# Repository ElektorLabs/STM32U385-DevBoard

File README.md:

# Elektor STM32U385 Dev Board: Arduino support

Arduino IDE support for the Elektor STM32U385 development board (schematic
260660-002, Rev 1.0), built on the official
[STM32duino](https://github.com/stm32duino/Arduino_Core_STM32) core.

What you get:

- **Board package (`elektor:stm32:u385board`):**
  - Every pin is named after the board, so you don't need the schematic:
    `LED1_A`, `BUTTON_USER1`, `SD_CS`, `GROVE_I2C_POWER`, `MIKROBUS_CS`, ...
  - `Serial` is the USB serial port; `Serial1`, `Wire` and `SPI` sit on the
    right header pins.
  - Uploads go over USB: BOOT + RESET, then *Upload*. An optional
    auto-reset method needs no buttons at all.
- **Elektor STM32U385 Dev Board library** (`U385Board.h`): LEDs, debounced
  buttons, clock switching, MCO output, temperature, VDDA, unique ID, reset
  cause and SMPS/LDO selection.
- **Nine examples:** LED cycle, LEDs with buttons, USB serial, board info,
  clock switching, low-power modes, Grove I2C scanner, microSD card and a
  mikroBUS Click tester.

| | |
|---|---|
| MCU | STM32U385RGT6Q: Cortex-M33, 96 MHz, 1 MB flash, 256 KB SRAM, SMPS package |
| USB | USB-C, full speed (CDC serial and ROM DFU bootloader) |
| Clocks | MSIS 96 MHz (default), HSI48 + CRS for USB, 16 MHz HSE crystal, 32.768 kHz LSE crystal |
| On board | 2 × two-colour LEDs (4 channels), User1/User2/Boot/Reset buttons, microSD, Grove I2C (switched), Grove/UART header, Qwiic, mikroBUS, Arduino Uno headers, LiPo charger |

## Documentation

| Document | Read it when |
|---|---|
| This README | Overview, pin names, library overview, examples, known issues |
| [Windows install](docs/windows-install.md) | Installing on Windows, in five steps |
| [Install guide](src/README.md) | Installing on Linux, macOS or Windows; arduino-cli, git links, Tools menu |
| [Pinout drawing](docs/pinout.png) ([SVG](docs/pinout.svg)) | Quick look at every header pin, connector, LED and button |
| [Pin guide](docs/pin-guide.md) | Wiring something up: every header pin, connector, on-board part and board name, plus the power section |
| [Board top](docs/board-top.png) / [bottom](docs/board-bottom.png) | Finding a part or connector on the PCB |
| [Schematic](docs/schematic-260660-002.png) | You need to trace a signal or check a component value |
| [How uploading works](docs/uploading.md) | Upload fails, the board stays in DFU, or you want to know what the button-free upload does |
| [Board and software overview](docs/board-and-software-overview.md) | Everything in one document: v1.1 changes, board package, library, all examples with code, upload internals, bring-up (source for the article) |
| [Problems and solutions](docs/problems-and-solutions.md) | Background: every hurdle during bring-up and how it was solved, including the drawbacks of button-free upload |
| [`U385Board.h`](src/Arduino/libraries/Elektor_STM32U385_DevBoard/src/U385Board.h) | Library reference: every function, with a comment explaining it |
| [`variant_U385_BOARD.h`](src/Arduino15/packages/elektor/hardware/stm32/1.0.0/variants/U385_BOARD/variant_U385_BOARD.h) | All pin numbers and board names as the compiler sees them |
| [Examples](src/Arduino/libraries/Elektor_STM32U385_DevBoard/examples) | Working code for every part of the board (also under *File → Examples → Elektor STM32U385 Dev Board*) |

## Repository layout

```
hardware/                          KiCad design files (board v1.1)
src/                               software; install guide in src/README.md
  Arduino15/                       paste "packages" into your Arduino15 folder
    packages/elektor/hardware/stm32/1.0.0/   the board package
      boards.txt, platform.txt     board definition, upload tool
      variants/U385_BOARD/         pin map, clock setup, button-free upload hook
      tools/dfu-upload.sh          upload script (dfu-util)
      tools/win/                   Windows: put dfu-util.exe here
      tools/linux/99-elektor-u385.rules   udev rule for Linux
  Arduino/                         paste "libraries" into your sketchbook
    libraries/Elektor_STM32U385_DevBoard/    the Arduino library
      src/U385Board.h, .cpp
      examples/                    00_LedCycle ... 08_MikroBus
docs/                              guides, pinout, schematic, board renders
  pin-guide.md                     every pin, connector and board name
  windows-install.md               Windows install in five steps
  uploading.md                     how the button-free upload works, recovery
  problems-and-solutions.md        hurdles during bring-up and how they were solved
  board-and-software-overview.md   everything in one document, with code
  schematic-260660-002.png         schematic
  pinout.png, pinout.svg           pinout drawing (made by docs/make_pinout.py)
  board-top.png, -bottom.png       board renders
```

## Getting started

1. Install **STM32 MCU based boards** 3.1.0 or newer from the Boards Manager.
2. Copy two folders from `src` (each merges with the folder already there):

   | Copy this | Windows | Linux | macOS |
   |---|---|---|---|
   | `src/Arduino15/packages` | `%LOCALAPPDATA%\Arduino15` | `~/.arduino15` | `~/Library/Arduino15` |
   | `src/Arduino/libraries` | `Documents\Arduino` | `~/Arduino` | `~/Documents/Arduino` |

3. Install dfu-util and the USB driver (Windows) or udev rule (Linux).
4. Put the board in DFU mode once (hold BOOT, press RESET) and upload
   *File → Examples → Elektor STM32U385 Dev Board → 00_LedCycle*.

Step by step: [Windows install](docs/windows-install.md) ·
[all systems, plus arduino-cli and git](src/README.md).

## Using the board

### Pin names

Use the board names; the STM32 names (`PA5`) and Arduino numbers (`13`) also
work. [docs/pin-guide.md](docs/pin-guide.md) has the full table with
connectors and schematic references.

The Arduino Uno headers are numbered as on any Uno, and each number is
mapped to the STM32 pin wired to that header position. These three lines
all drive the same pin, the D13 header pin (PA5):

```cpp
digitalWrite(13, HIGH);     // Arduino number
digitalWrite(D13, HIGH);    // Arduino name
digitalWrite(PA5, HIGH);    // STM32 name
```

| Header | STM32 | | Header | STM32 | | Header | STM32 |
|---|---|---|---|---|---|---|---|
| D0 | PA10 | | D6 | PB10 | | D12 | PA6 |
| D1 | PA9 | | D7 | PC6 | | D13 | PA5 |
| D2 | PC9 | | D8 | PC7 | | D14 | PB7 |
| D3 | PB13 | | D9 | PA8 | | D15 | PB6 |
| D4 | PB14 | | D10 | PA15 | | A0 / A1 / A2 | PA0 / PA1 / PA2 |
| D5 | PB15 | | D11 | PA7 | | A3 / A4 / A5 | PC1 / PA3 / PB1 |

The mapping is in
[`variant_U385_BOARD.h`](src/Arduino15/packages/elektor/hardware/stm32/1.0.0/variants/U385_BOARD/variant_U385_BOARD.h)
and was verified for every header pin with compile-time checks
(`static_assert(D13 == PA5)`, `static_assert(A3 == PC1)`, ...). The same pairs are printed on the pinout drawing.

| Name | Pin | What |
|---|---|---|
| `LED1_A` (`LED_BUILTIN`), `LED1_B` | PC10, PC11 | LED1, active high |
| `LED2_A`, `LED2_B` | PC12, PB4 | LED2, active high |
| `BUTTON_USER1` (`USER_BTN`) | PB5 | SW2 "User1", HIGH when pressed |
| `BUTTON_USER2` | PB2 | SW1 "User2", HIGH when pressed |
| `GROVE_I2C_POWER` | PA4 | HIGH turns on 3V3 at the Grove I2C socket K4 |
| `SD_CS`, `SD_DETECT` | PC8, PD2 | microSD over SPI; detect LOW = card in |
| `MIKROBUS_AN/RST/CS/PWM/INT` | PA0, PC3, PB0, PB10, PC9 | mikroBUS sockets J5/J6 |
| `MCO_PIN` | PA8 (D9) | clock output |
| `D0`–`D15`, `A0`–`A5` | Arduino Uno headers | |

| Object | Pins | Connected to |
|---|---|---|
| `Serial` | USB | USB-C (virtual COM port) |
| `Serial1` | PA10 RX / PA9 TX | D0/D1, UART header K6, mikroBUS J6 |
| `Wire` | PB7 SDA / PB6 SCL | Grove I2C K4, Qwiic K8, mikroBUS, J4; 4.7 kΩ pull-ups on board |
| `SPI` | PA5 SCK / PA6 MISO / PA7 MOSI, SS PA15 | D10–D13, mikroBUS J5, microSD |

Plain Arduino, no library needed:

```cpp
void setup() {
  pinMode(LED1_A, OUTPUT);
  pinMode(BUTTON_USER1, INPUT);           // external 10k pull-down on board
}
void loop() {
  digitalWrite(LED1_A, digitalRead(BUTTON_USER1) == BUTTON_PRESSED);
}
```

### The library (`U385Board.h`)

```cpp
#include <U385Board.h>

void setup() {
  Serial.begin(115200);
  Board.begin();                    // LEDs off, buttons as inputs
}

void loop() {
  Board.update();                   // debounce the buttons, call every loop
  if (Board.pressed(USER1)) Board.ledToggle(0);
  if (Board.heldFor(USER2) > 1000) Board.ledsAll(true);
}
```

| Area | Functions |
|---|---|
| LEDs (index 0–3 = PC10, PC11, PB4, PC12) | `led(i, on)`, `ledToggle(i)`, `ledState(i)`, `ledsOff()`, `ledsAll(on)`, `ledsShow(bits)`, `ledPin(i)` |
| Buttons (`USER1`, `USER2`) | `update()`, `isDown(b)`, `pressed(b)`, `released(b)`, `heldFor(b)`, `readRaw(b)`, `releasedLevel(b)`, `setDebounce(ms)` |
| Board | `groveI2CPower(on)`, `sdCardPresent()`, `enterBootloader()`, `useSMPS(on)`, `smpsActive()` |
| Clocks | `setSystemClock(SYSCLK_96MHZ … SYSCLK_3MHZ)`, `systemClock()`, `hclk()`, `pclk1/2/3()`, `systemClockSource()`, `startLSE()`, `startHSE()`, `msiPllLock()`, `clockOut(source, div)`, `printClocks(Serial)` |
| Chip | `uniqueId()`, `flashSizeKB()`, `resetCause()`, `temperatureC()`, `vdda()` |

Notes:

- **Button polarity.** `Board.begin()` takes the button level at start-up as
  "released", so the library works whichever way the buttons are wired.
  Don't hold a button while the sketch starts.
- **Slow clocks and USB.** USB needs at least 12 MHz. At 6 MHz and 3 MHz the
  USB serial port stops until you go back up.
- **After `setSystemClock()`,** call `Serial1.begin()` / `Wire.setClock()`
  again so their dividers match the new clock. `millis()` and `delay()`
  adjust by themselves.
- **SMPS.** `useSMPS()` switches the core supply from the LDO to the on-board
  SMPS (L1). Expect lower current, mainly at 96 MHz. Switching was tested both
  ways at 96 MHz; the current saving has not been measured yet.
- **After Shutdown** the sketch restarts and `resetCause()` reports
  "power-on / brown-out", the way the chip flags a shutdown exit.

### Examples

*File → Examples → Elektor STM32U385 Dev Board*:

| Example | What it shows | Tested on hardware |
|---|---|---|
| `00_LedCycle` | The four LEDs run through seven patterns: chase, bounce, fill, alternate, LED1 vs LED2, binary count, flash | ✅ |
| `01_LedCycleButtons` | User1 = next LED, User2 = previous, hold User1 1 s = auto-run; button levels printed on serial | ⏳ not yet tested with the buttons |
| `02_SerialMonitor` | USB serial command shell: `1`–`4` toggle LEDs, `a` all, `o` off, `c` clocks, `i` info, `b` bootloader | ✅ |
| `03_BoardInfo` | Clocks, unique ID, flash size, reset cause, die temperature, VDDA, regulator, SD card | ✅ |
| `04_ClockSwitch` | Steps SYSCLK 96 → 48 → 24 → 12 MHz with `n`; `l` locks MSI to the LSE crystal; MCO on D9 | ✅ |
| `05_LowPowerModes` | Sleep, Stop (deep sleep) and Shutdown, woken by a button or an RTC alarm after 10 s (all three modes over serial) | ✅ RTC wake; button wake not yet tested |
| `06_GroveI2CScanner` | Turns on Grove power and scans the I2C bus | ✅ |
| `07_SDCard` | microSD over SPI with SdFat (FAT16, FAT32 and exFAT): card info, file list, append/read/delete a log file, hot-plug via card detect | ✅ 64 GB SDXC, exFAT |
| `08_MikroBus` | Click board test tool: reset, AN and INT levels, I2C scan, SPI read-ID, PWM, and a USB-to-UART bridge for AT-command clicks | ✅ socket empty; no Click board tested yet |

## Known issues

- **A sketch that disables USB, crashes or sleeps** cannot be reset into DFU
  from the IDE. Use BOOT + RESET.
- **Stack size.** STM32duino 3.1.0's linker script for the U3 sets a 1 KB
  stack, and the startup code makes that a hard limit (MSPLIM). Going past it
  locks the chip up, USB included. It happened with SdFat creating a file.
  This board package raises the stack to 16 KB in its own linker script.
  Other STM32U3 boards in STM32duino still have the 1 KB limit.
- **Tested on Linux** with arduino-cli 1.3.0 and STM32duino 3.1.0, and on
  **Windows** with Arduino IDE 2.x: copy-and-paste install, upload in DFU
  mode and button-free upload. macOS is untested; please report how it goes.

## License

- The board package, library, examples and docs are released under the MIT
  License (see `LICENSE`).
- `src/Arduino15/packages/elektor/hardware/stm32/1.0.0/variants/U385_BOARD/PeripheralPins.c`, `PinNamesVar.h` and `ldscript.ld`
  come from the STM32duino core. They remain © STMicroelectronics under the
  BSD-3-Clause license given in each file's header.

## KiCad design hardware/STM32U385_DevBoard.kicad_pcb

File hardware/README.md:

# Hardware

KiCad project for the Elektor STM32U385 Dev Board (260660), board revision
v1.1.

| Path | What |
|---|---|
| `STM32U385_DevBoard.kicad_pro` | KiCad project: open this |
| `STM32U385_DevBoard.kicad_sch` | Schematic |
| `STM32U385_DevBoard.kicad_pcb` | PCB layout |
| `stm32u385-uno-schematic.pdf` | Schematic as PDF |
| `MySym/`, `MyLib.pretty/`, `DevBoard4.pretty/` | Project symbols and footprints |
| `3D Models/` | STEP models for the 3D view |
| `Data_Sheets/` | Datasheets of the main parts |
| `plots/` | Assembly drawing (PDF) |
| `production/` | Fabrication ZIP: Gerbers, drill and placement files |

v1.1 moves the buttons: RESET and BOOT sit on the left edge next to USB-C,
USER1 and USER2 at the bottom left next to the barrel jack, so they are
easier to press. The MCU pins are unchanged, so the same board package and
library work on v1.0 and v1.1. [docs/pin-guide.md](../docs/pin-guide.md) and
the [pinout drawing](../docs/pinout.png) list every pin and connector.

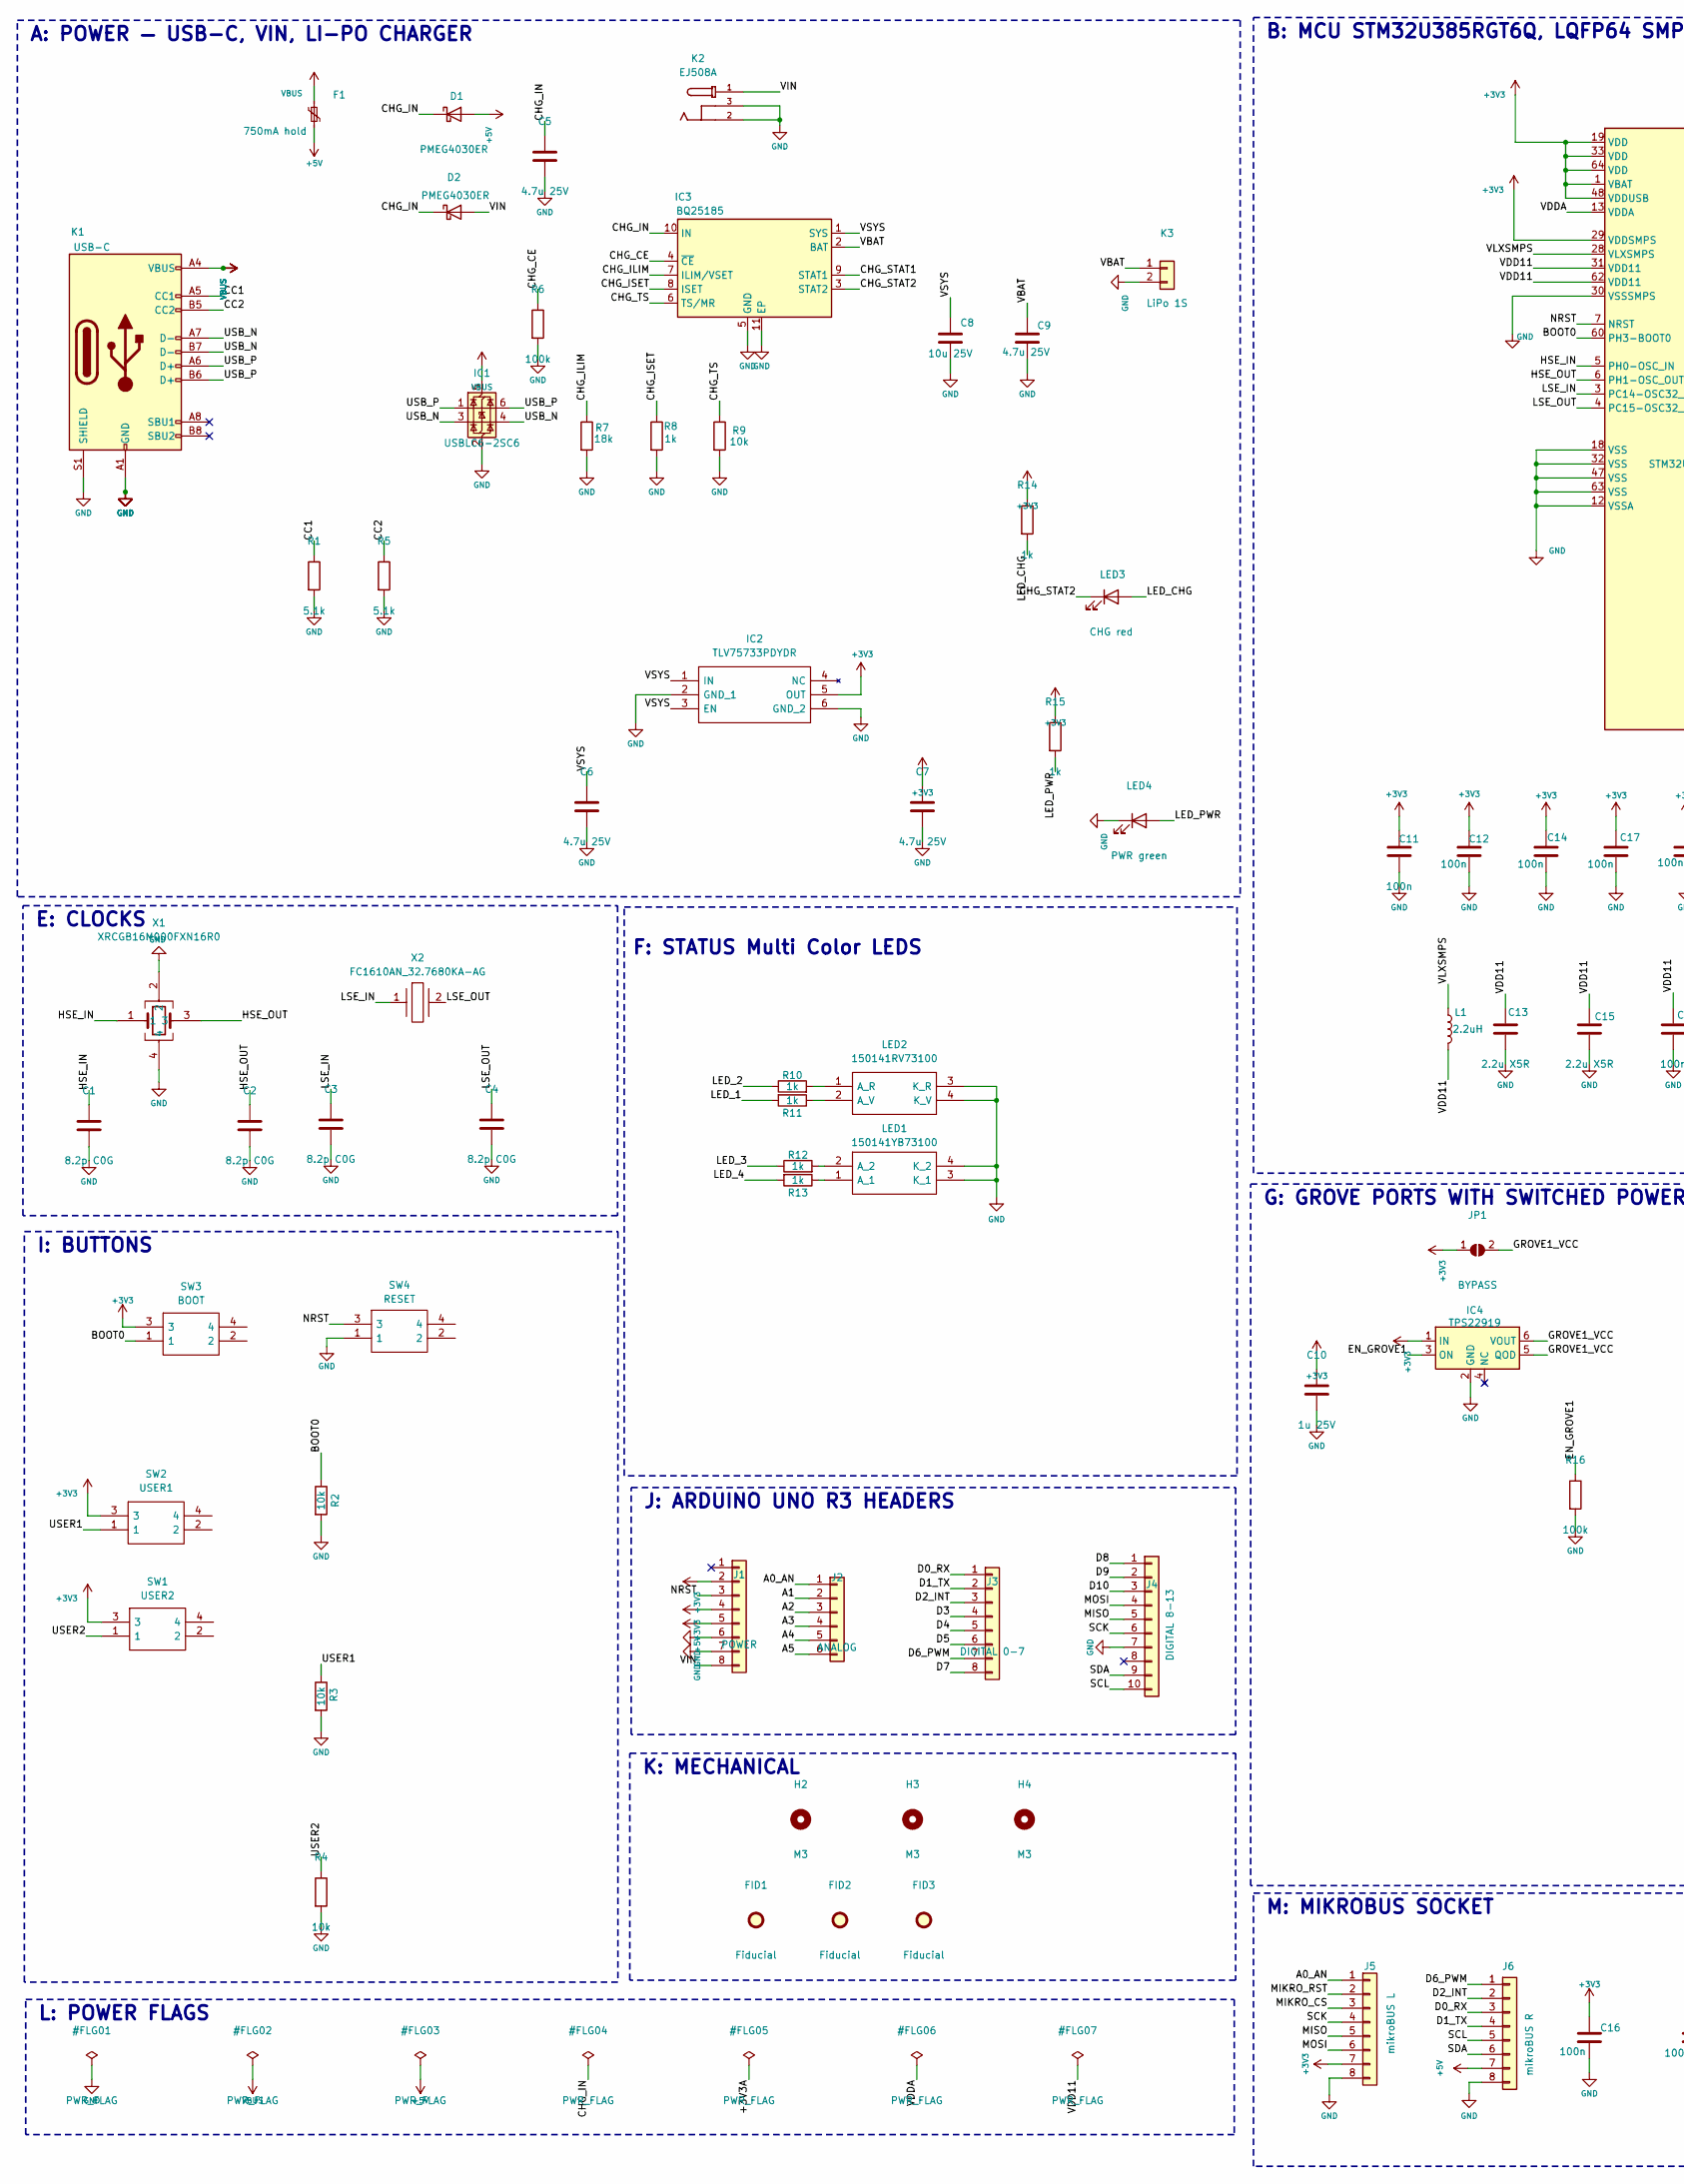
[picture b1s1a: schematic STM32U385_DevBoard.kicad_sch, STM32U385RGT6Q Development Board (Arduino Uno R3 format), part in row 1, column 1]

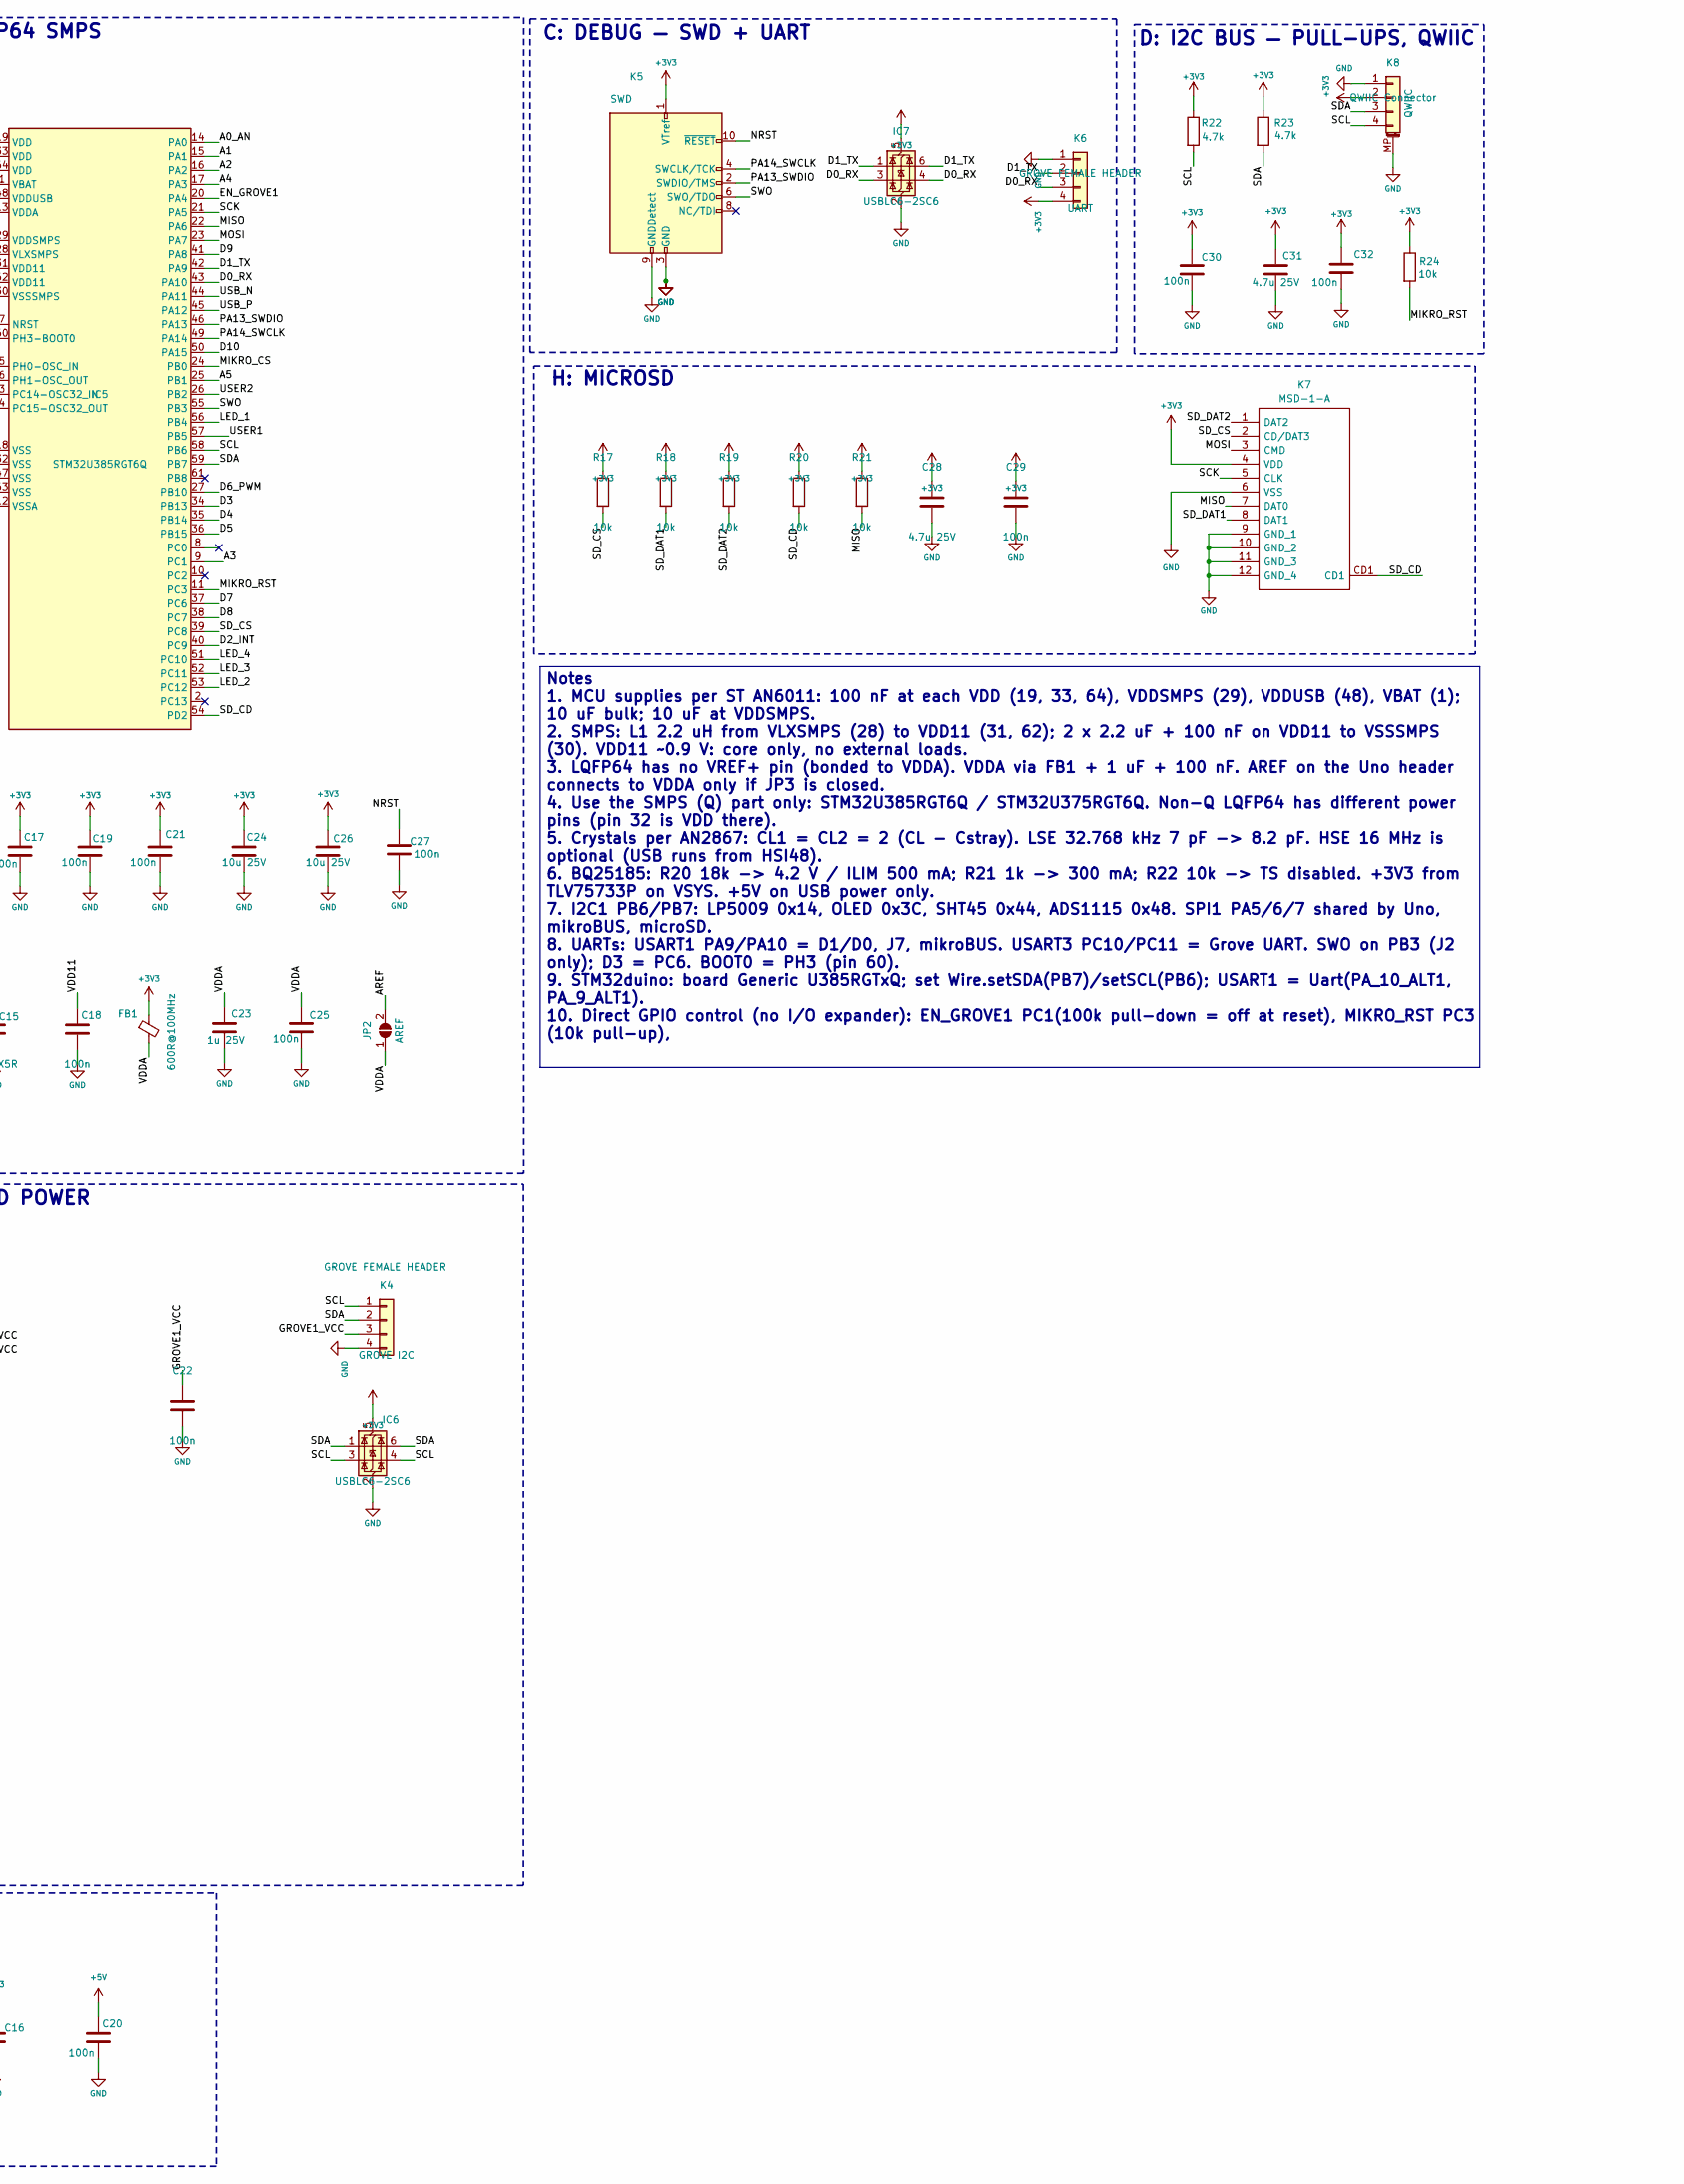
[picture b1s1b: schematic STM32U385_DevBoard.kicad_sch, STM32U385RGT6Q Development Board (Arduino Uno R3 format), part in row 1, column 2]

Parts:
C1, C2, C3, C4: 8.2p C0G; Capacitor_SMD__C_0402_1005Metric_c6f3790037; MPN GRM1555C1H8R2BA01D
C5, C6, C7, C9, C28, C31: 4.7u 25V; Capacitor_SMD__C_0603_1608Metric_922116857e; MPN GRM188R61E475KE11J
C8, C24, C26: 10u 25V; Capacitor_SMD__C_0805_2012Metric_aa5599db5b; MPN GRM21BR61E106KA73L
C10, C23: 1u 25V; Capacitor_SMD__C_0402_1005Metric_c6f3790037; MPN CL05A105KA5NQNC
C11, C12, C14, C16, C17, C18, C19, C20, C21, C22, C25, C27, C29, C30, C32: 100n; Capacitor_SMD__C_0402_1005Metric_c6f3790037; MPN GRM155R71C104KA88D
C13, C15: 2.2u X5R; Capacitor_SMD__C_0603_1608Metric_922116857e; MPN GRM188R61C225KE15D
D1, D2: PMEG4030ER; Diode_SMD__Nexperia_CFP3_SOD-123W_821266d4fc; MPN PMEG4030ER,115
F1: 750mA hold; Fuse__Fuse_0805_2012Metric_43cd33858f; MPN MF-PSMF075X-2
FB1: 600R@100MHz; Inductor_SMD__L_0603_1608Metric_cc9b436813; MPN BLM18KG601SN1D
FID1, FID2, FID3: Fiducial; Fiducial__Fiducial_1mm_Mask2mm_55869b6f71
H2, H3, H4: M3; DevBoard4__MountingHole_3.2mm_Uno_991e85bc9b
IC1, IC6, IC7: USBLC6-2SC6; Package_TO_SOT_SMD__SOT-23-6_bee7fafe0c; MPN USBLC6-2SC6
IC2: TLV75733PDYDR; Mouser Part Number 595-TLV75733PDYDR
IC3: BQ25185; DevBoard4__TI_DLH0010A_WSON-10_2x2.2mm_P0.4mm_301ec00fd8; MPN BQ25185DLHR
IC4: TPS22919; Package_TO_SOT_SMD__SOT-363_SC-70-6_8457b2c561; MPN TPS22919DCKR
IC5: STM32U385RGT6Q; Package_QFP__LQFP-64_10x10mm_P0.5mm_5fbfdbce52; MPN STM32U385RGT6Q
J1: POWER; Connector_PinSocket_2.54mm__PinSocket_1x08_P2.54mm_Vertical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; MPN 61300811821
J2: ANALOG; Connector_PinSocket_2.54mm__PinSocket_1x06_P2.54mm_Vertical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; MPN 61300611821
J3: DIGITAL 0-7; Connector_PinSocket_2.54mm__PinSocket_1x08_P2.54mm_Vertical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; MPN 61300811821
J4: DIGITAL 8-13; Connector_PinSocket_2.54mm__PinSocket_1x10_P2.54mm_Vertical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; MPN 61301011821
J5: mikroBUS L; Connector_PinSocket_2.54mm__PinSocket_1x08_P2.54mm_Vertical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; MPN 61300811821
J6: mikroBUS R; Connector_PinSocket_2.54mm__PinSocket_1x08_P2.54mm_Vertical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; MPN 61300811821
JP1: BYPASS; Jumper__SolderJumper-2_P1.3mm_Open_RoundedPad1.0x1.5mm_8996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
JP2: AREF; Jumper__SolderJumper-2_P1.3mm_Open_RoundedPad1.0x1.5mm_8996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
K1: USB-C; Connector_USB__USB_C_Receptacle_GCT_USB4105-xx-A_16P_TopMnt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; MPN USB4105-GF-A
K2: EJ508A; footprints10__MPD_EJ508A_cdcfbdb686; PARTREV J
K3: LiPo 1S; Connector_JST__JST_PH_S2B-PH-SM4-TB_1x02-1MP_P2.00mm_Horizo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; MPN S2B-PH-SM4-TB(LF)(SN)
K4: GROVE I2C; Connector_JST__JST_PH_S4B-PH-SM4-TB_1x04-1MP_P2.00mm_Horizo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; MPN 1597-114020164-ND
K5: SWD; Connector_PinHeader_1.27mm__PinHeader_2x05_P1.27mm_Vertical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; MPN 20021121-00010C4LF
K6: UART; Connector_JST__JST_PH_S4B-PH-SM4-TB_1x04-1MP_P2.00mm_Horizo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; MPN 1597-114020164-ND
K7: MSD-1-A; SamacSys_Parts__MSD1A_9faa34f890; Mouser Part Number 179-MSD-1-A
K8: QWIIC; Connector_JST__JST_SH_SM04B-SRSS-TB_1x04-1MP_P1.00mm_Horizo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; MPN SM04B-SRSS-TB
L1: 2.2uH; Inductor_SMD__L_0805_2012Metric_28a6f4f15e
LED1: 150141YB73100; SamacSys_Parts__150141RV73100_c801ef0791; Mouser Part Number 710-150141YB73100
LED2: 150141RV73100; SamacSys_Parts__150141RV73100_c801ef0791; Mouser Part Number 710-150141RV73100
LED3: CHG red; LED_SMD__LED_0603_1608Metric_041a55222f; MPN LTST-C191KRKT
LED4: PWR green; LED_SMD__LED_0603_1608Metric_041a55222f; MPN LTST-C191KGKT
R1, R5: 5.1k; Resistor_SMD__R_0402_1005Metric_a72d4a34ce; MPN RC0402FR-075K1L
R2, R3, R4, R9, R17, R18, R19, R20, R21, R24: 10k; Resistor_SMD__R_0402_1005Metric_a72d4a34ce; MPN RC0402FR-0710KL
R6, R16: 100k; Resistor_SMD__R_0402_1005Metric_a72d4a34ce; MPN RC0402FR-07100KL
R7: 18k; Resistor_SMD__R_0402_1005Metric_a72d4a34ce; MPN RC0402FR-0718KL
R8, R14, R15: 1k; Resistor_SMD__R_0402_1005Metric_a72d4a34ce; MPN RC0402FR-071KL
R10, R11, R12, R13: 1k; Resistor_SMD__R_0402_1005Metric_a72d4a34ce; MPN RC0402FR-0710KL
R22, R23: 4.7k; Resistor_SMD__R_0402_1005Metric_a72d4a34ce; MPN RC0402FR-074K7L
SW1: USER2; SKTHBAE010; Mouser Part Number 688-SKTHBAE010
SW2: USER1; SKTHBAE010; Mouser Part Number 688-SKTHBAE010
SW3: BOOT; SKTHBAE010; Mouser Part Number 688-SKTHBAE010
SW4: RESET; SKTHBAE010; Mouser Part Number 688-SKTHBAE010
X1: XRCGB16M000FXN16R0; XRCGB; Mouser Part Number 81-XRCGB16M000FXN16R
X2: FC1610AN_32.7680KA-AG; FC1610AN327680KAAG; Mouser Part Number 732-AN32.7680KA-AG

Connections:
+3V3: C7.1, C10.1, C11.1, C12.1, C14.1, C16.1, C17.1, C19.1, C21.1, C24.1, C26.1, C28.1, C29.1, C30.1, C31.1, C32.1, FB1.1, IC2.5 (OUT), IC4.1 (IN), IC5.1 (VBAT), IC5.19 (VDD), IC5.29 (VDDSMPS), IC5.33 (VDD), IC5.48 (VDDUSB), IC5.64 (VDD), IC6.5 (VBUS), IC7.5 (VBUS), J1.2, J1.4, J5.7, JP1.1 (A), K5.1 (VTref), K6.4, K7.4 (VDD), K8.2, R14.1, R15.1, R17.1, R18.1, R19.1, R20.1, R21.1, R22.1, R23.1, R24.1, SW1.3, SW2.3, SW3.3
+5V: C20.1, D1.2 (A), F1.2, J1.5, J6.7
/A0_AN: IC5.14 (PA0), J2.1, J5.1
/A1: IC5.15 (PA1), J2.2
/A2: IC5.16 (PA2), J2.3
/A3: IC5.9 (PC1), J2.4
/A4: IC5.17 (PA3), J2.5
/A5: IC5.25 (PB1), J2.6
/AREF: JP2.2 (B)
/BOOT0: IC5.60 (PH3-BOOT0), R2.1, SW3.1
/CC1: K1.A5 (CC1), R1.1
/CC2: K1.B5 (CC2), R5.1
/CHG_CE: IC3.4 (~CE), R6.1
/CHG_ILIM: IC3.7 (ILIM/VSET), R7.1
/CHG_IN: C5.1, D1.1 (K), D2.1 (K), IC3.10 (IN)
/CHG_ISET: IC3.8 (ISET), R8.1
/CHG_STAT1: IC3.9 (STAT1)
/CHG_STAT2: IC3.3 (STAT2), LED3.1 (K)
/CHG_TS: IC3.6 (TS/MR), R9.1
/D0_RX: IC5.43 (PA10), IC7.3 (I/O2), IC7.4 (I/O2), J3.1, J6.3, K6.3
/D1_TX: IC5.42 (PA9), IC7.1 (I/O1), IC7.6 (I/O1), J3.2, J6.4, K6.2
/D2_INT: IC5.40 (PC9), J3.3, J6.2
/D3: IC5.34 (PB13), J3.4
/D4: IC5.35 (PB14), J3.5
/D5: IC5.36 (PB15), J3.6
/D6_PWM: IC5.27 (PB10), J3.7, J6.1
/D7: IC5.37 (PC6), J3.8
/D8: IC5.38 (PC7), J4.1
/D9: IC5.41 (PA8), J4.2
/D10: IC5.50 (PA15), J4.3
/EN_GROVE1: IC4.3 (ON), IC5.20 (PA4), R16.1
/GROVE1_VCC: C22.1, IC4.5 (QOD), IC4.6 (VOUT), JP1.2 (B), K4.3
/HSE_IN: C1.1, IC5.5 (PH0-OSC_IN), X1.1
/HSE_OUT: C2.1, IC5.6 (PH1-OSC_OUT), X1.3
/LED_1: IC5.56 (PB4), R11.2
/LED_2: IC5.53 (PC12), R10.1
/LED_3: IC5.52 (PC11), R12.1
/LED_4: IC5.51 (PC10), R13.2
/LED_CHG: LED3.2 (A), R14.2
/LED_PWR: LED4.2 (A), R15.2
/LSE_IN: C3.1, IC5.3 (PC14-OSC32_IN), X2.1
/LSE_OUT: C4.1, IC5.4 (PC15-OSC32_OUT), X2.2
/MIKRO_CS: IC5.24 (PB0), J5.3
/MIKRO_RST: IC5.11 (PC3), J5.2, R24.2
/MISO: IC5.22 (PA6), J4.5, J5.5, K7.7 (DAT0), R21.2
/MOSI: IC5.23 (PA7), J4.4, J5.6, K7.3 (CMD)
/NRST: C27.1, IC5.7 (NRST), J1.3, K5.10 (~RESET), SW4.3
/PA13_SWDIO: IC5.46 (PA13), K5.2 (SWDIO/TMS)
/PA14_SWCLK: IC5.49 (PA14), K5.4 (SWCLK/TCK)
/SCK: IC5.21 (PA5), J4.6, J5.4, K7.5 (CLK)
/SCL: IC5.58 (PB6), IC6.3 (I/O2), IC6.4 (I/O2), J4.10, J6.5, K4.1, K8.4, R22.2
/SDA: IC5.59 (PB7), IC6.1 (I/O1), IC6.6 (I/O1), J4.9, J6.6, K4.2, K8.3, R23.2
/SD_CD: IC5.54 (PD2), K7.CD1, R20.2
/SD_CS: IC5.39 (PC8), K7.2 (CD/DAT3), R17.2
/SD_DAT1: K7.8 (DAT1), R18.2
/SD_DAT2: K7.1 (DAT2), R19.2
/SWO: IC5.55 (PB3), K5.6 (SWO/TDO)
/USB_N: IC1.3 (I/O2), IC1.4 (I/O2), IC5.44 (PA11), K1.A7 (D-), K1.B7 (D-)
/USB_P: IC1.1 (I/O1), IC1.6 (I/O1), IC5.45 (PA12), K1.A6 (D+), K1.B6 (D+)
/USER1: IC5.57 (PB5), R3.1, SW2.1
/USER2: IC5.26 (PB2), R4.1, SW1.1
/VBAT: C9.1, IC3.2 (BAT), K3.1
/VDD11: C13.1, C15.1, C18.1, IC5.31 (VDD11), IC5.62 (VDD11), L1.2
/VDDA: C23.1, C25.1, FB1.2, IC5.13 (VDDA), JP2.1 (A)
/VIN: D2.2 (A), J1.8, K2.1
/VLXSMPS: IC5.28 (VLXSMPS), L1.1
/VSYS: C6.1, C8.1, IC2.1 (IN), IC2.3 (EN), IC3.1 (SYS)
GND: C1.2, C2.2, C3.2, C4.2, C5.2, C6.2, C7.2, C8.2, C9.2, C10.2, C11.2, C12.2, C13.2, C14.2, C15.2, C16.2, C17.2, C18.2, C19.2, C20.2, C21.2, C22.2, C23.2, C24.2, C25.2, C26.2, C27.2, C28.2, C29.2, C30.2, C31.2, C32.2, IC1.2 (GND), IC2.2 (GND_1), IC2.6 (GND_2), IC3.5 (GND), IC3.11 (EP), IC4.2 (GND), IC5.12 (VSSA), IC5.18 (VSS), IC5.30 (VSSSMPS), IC5.32 (VSS), IC5.47 (VSS), IC5.63 (VSS), IC6.2 (GND), IC7.2 (GND), J1.6, J1.7, J4.7, J5.8, J6.8, K1.A1 (GND), K1.A12 (GND), K1.B1 (GND), K1.B12 (GND), K1.S1 (SHIELD), K2.2, K2.3, K3.2, K4.4, K5.3 (GND), K5.5 (GND), K5.9 (GNDDetect), K6.1, K7.6 (VSS), K7.9 (GND_1), K7.10 (GND_2), K7.11 (GND_3), K7.12 (GND_4), K8.1, K8.MP (MountPin), LED1.3 (K_1), LED1.4 (K_2), LED2.3 (K_R), LED2.4 (K_V), LED4.1 (K), R1.2, R2.2, R3.2, R4.2, R5.2, R6.2, R7.2, R8.2, R9.2, R16.2, SW4.1, X1.2, X1.4
unnamed: LED1.1 (A_1), R13.1
unnamed: LED1.2 (A_2), R12.2
unnamed: LED2.1 (A_R), R10.2
unnamed: LED2.2 (A_V), R11.1
VBUS: F1.1, IC1.5 (VBUS), K1.A4 (VBUS), K1.A9 (VBUS), K1.B4 (VBUS), K1.B9 (VBUS)

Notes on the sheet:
G: GROVE PORTS WITH SWITCHED POWER
E: CLOCKS
H: MICROSD
I: BUTTONS
D: I2C BUS — PULL-UPS, QWIIC
L: POWER FLAGS
J: ARDUINO UNO R3 HEADERS
K: MECHANICAL
A: POWER — USB-C, VIN, LI-PO CHARGER
C: DEBUG — SWD + UART
B: MCU STM32U385RGT6Q, LQFP64 SMPS
M: MIKROBUS SOCKET
F: STATUS Multi Color LEDS
Notes 1. MCU supplies per ST AN6011: 100 nF at each VDD (19, 33, 64), VDDSMPS (29), VDDUSB (48), VBAT (1); 10 uF bulk; 10 uF at VDDSMPS. 2. SMPS: L1 2.2 uH from VLXSMPS (28) to VDD11 (31, 62); 2 x 2.2 uF + 100 nF on VDD11 to VSSSMPS (30). VDD11 ~0.9 V: core only, no external loads. 3. LQFP64 has no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

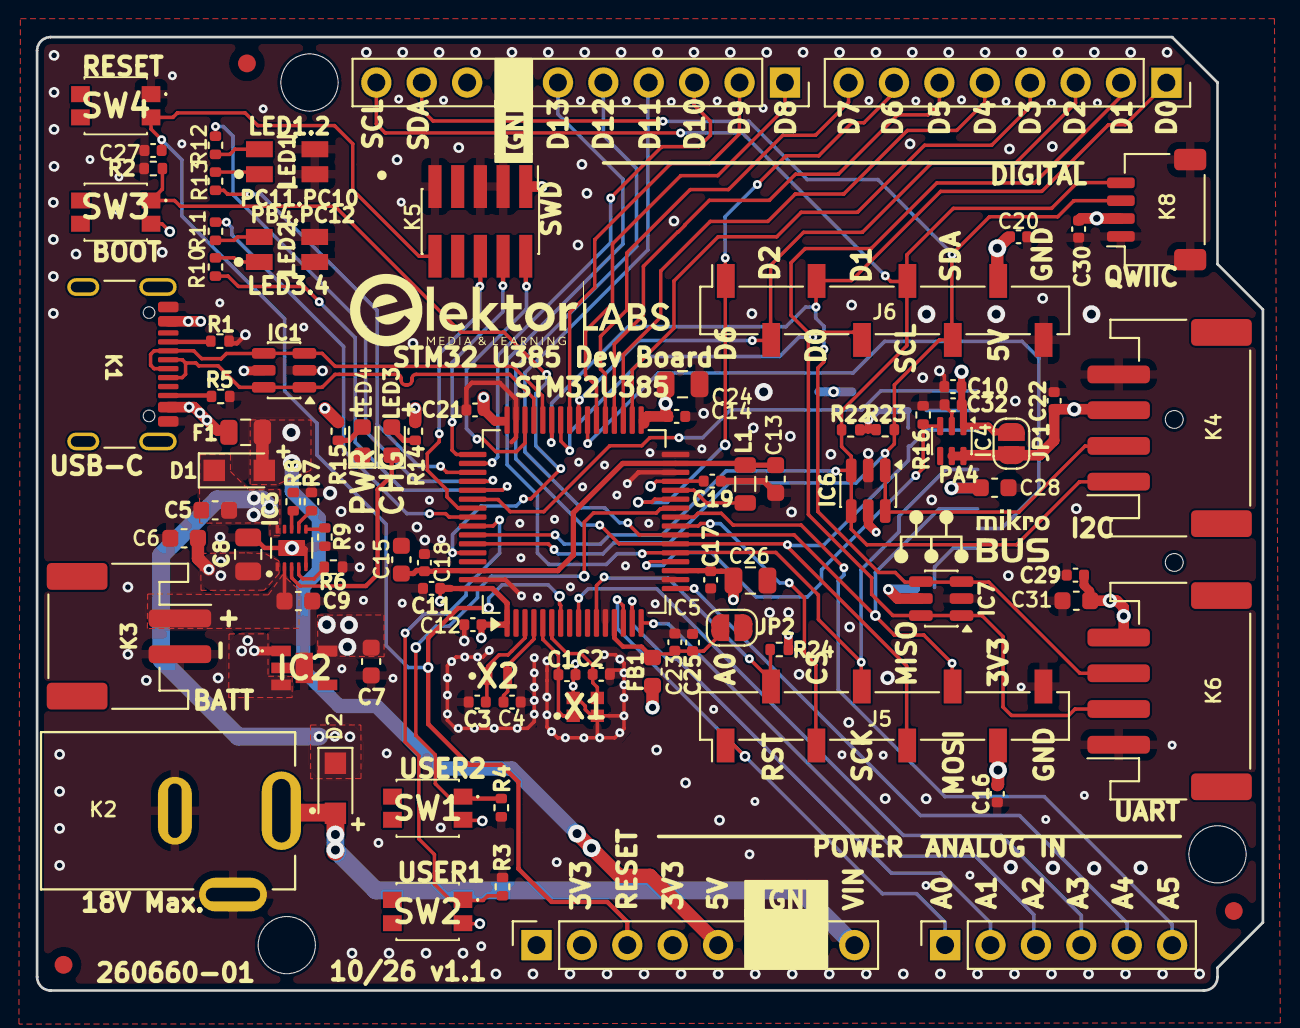
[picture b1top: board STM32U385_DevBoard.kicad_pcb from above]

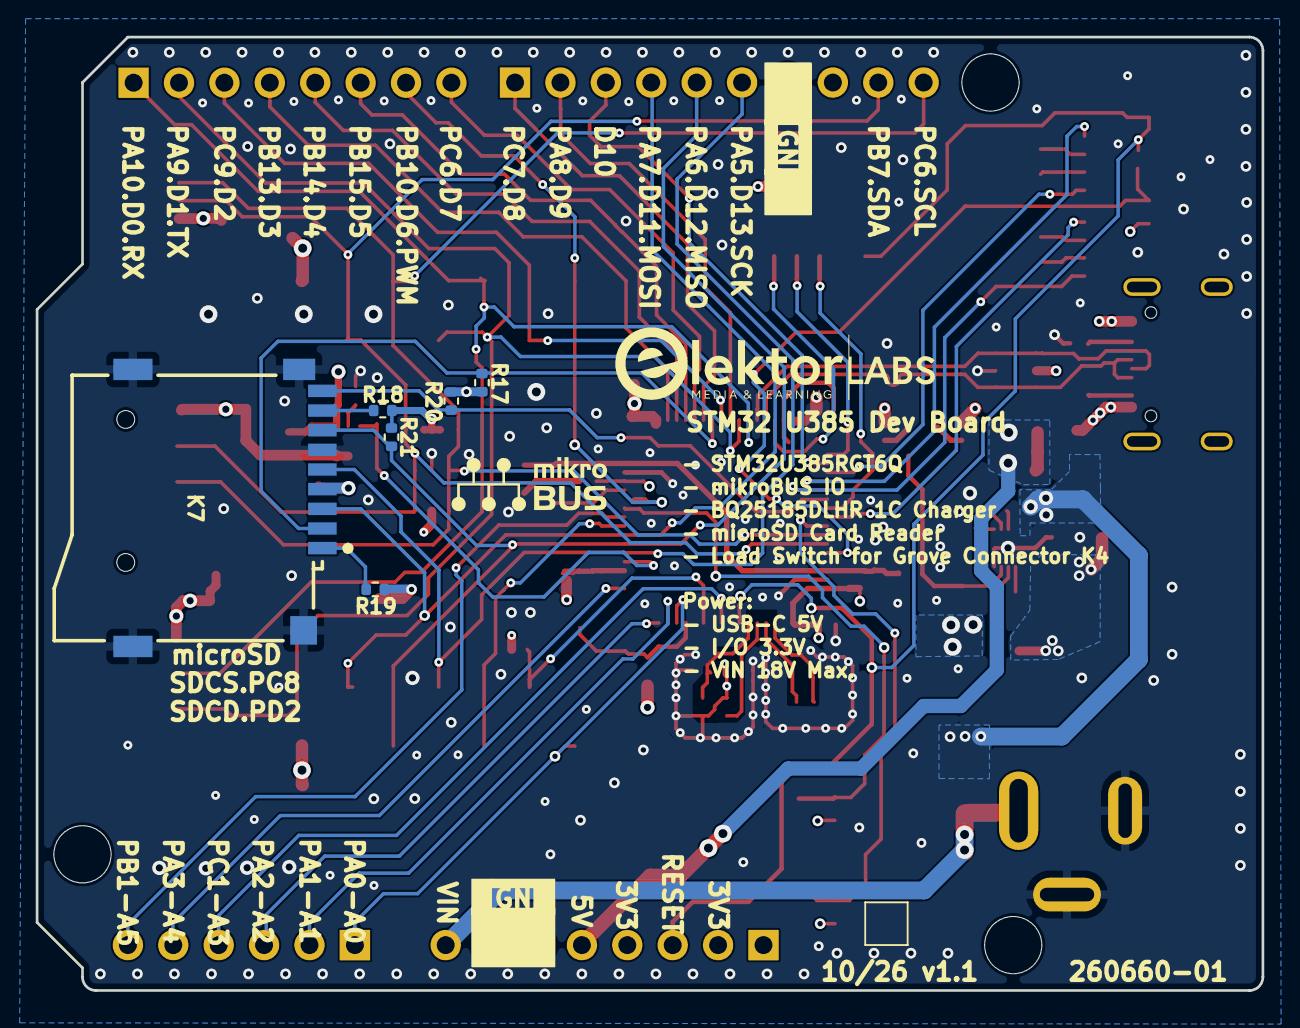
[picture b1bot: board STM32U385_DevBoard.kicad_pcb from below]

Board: 4 copper layers, 68.6 x 53.3 mm, 100 parts (6 on the bottom side), 71 nets.

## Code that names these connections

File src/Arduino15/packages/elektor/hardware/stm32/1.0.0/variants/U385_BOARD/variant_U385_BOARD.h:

/*
 * Arduino variant for the STM32U385RGT6Q board, schematic 260660-002 Rev 1.0
 *
 * Pin numbering
 *   D0..D13    Arduino Uno digital header (J3, J4)
 *   D14, D15   SDA, SCL on J4 (I2C1)
 *   D16..D27   on-board parts (LEDs, buttons, Grove power, mikroBUS, microSD, BOOT0)
 *   D28..D40   system pins and spare pins
 *   D41..D46   A0..A5 on the analog header (J2)
 *
 * STM32 pin names (PA5, PC10, ...) work everywhere a pin number is expected.
 * Logic level is 3.3 V on every pin.
 */
#pragma once

/*----------------------------------------------------------------------------
 *        STM32 pins number
 *----------------------------------------------------------------------------*/
// J3: Arduino digital header, low half
#define PA10                    0    // D0  USART1 RX (shared with Grove UART K6, mikroBUS J6)
#define PA9                     1    // D1  USART1 TX (shared with Grove UART K6, mikroBUS J6)
#define PC9                     2    // D2  mikroBUS INT
#define PB13                    3    // D3
#define PB14                    4    // D4
#define PB15                    5    // D5
#define PB10                    6    // D6  mikroBUS PWM
#define PC6                     7    // D7
// J4: Arduino digital header, high half
#define PC7                     8    // D8
#define PA8                     9    // D9  also MCO (clock output)
#define PA15                    10   // D10 SPI SS
#define PA7                     11   // D11 SPI1 MOSI
#define PA6                     12   // D12 SPI1 MISO
#define PA5                     13   // D13 SPI1 SCK
#define PB7                     14   // D14 I2C1 SDA
#define PB6                     15   // D15 I2C1 SCL
// On-board parts
#define PC10                    16   // LED1 pin 1 (R13)
#define PC11                    17   // LED1 pin 2 (R12)
#define PC12                    18   // LED2 pin 1 (R10)
#define PB4                     19   // LED2 pin 2 (R11)
#define PB5                     20   // SW2 "User1", HIGH when pressed
#define PB2                     21   // SW1 "User2", HIGH when pressed
#define PA4                     22   // Grove I2C power switch enable (IC4)
#define PC3                     23   // mikroBUS RST
#define PB0                     24   // mikroBUS CS
#define PC8                     25   // microSD CS
#define PD2                     26   // microSD card detect, LOW = card inserted
#define PH3                     27   // BOOT0 / SW3
// System and spare pins
#define PA13                    28   // SWDIO
#define PA14                    29   // SWCLK
#define PB3                     30   // SWO
#define PH0                     31   // HSE 16 MHz crystal
#define PH1                     32   // HSE 16 MHz crystal
#define PC14                    33   // LSE 32.768 kHz crystal
#define PC15                    34   // LSE 32.768 kHz crystal
#define PA11                    35   // USB D-
#define PA12                    36   // USB D+
#define PB8                     37   // not connected
#define PC0                     38   // not connected
#define PC2                     39   // not connected
#define PC13                    40   // not connected
// J2: Arduino analog header
#define PA0                     PIN_A0   // D41 A0, OPAMP1 VINP, mikroBUS AN
#define PA1                     PIN_A1   // D42 A1, OPAMP1 VINM
#define PA2                     PIN_A2   // D43 A2
#define PC1                     PIN_A3   // D44 A3
#define PA3                     PIN_A4   // D45 A4, OPAMP1 VOUT
#define PB1                     PIN_A5   // D46 A5

// Alternate pins number
#define PA1_ALT1                (PA1  | ALT1)
#define PA2_ALT1                (PA2  | ALT1)
#define PA3_ALT1                (PA3  | ALT1)
#define PA4_ALT1                (PA4  | ALT1)
#define PA5_ALT1                (PA5  | ALT1)
#define PA6_ALT1                (PA6  | ALT1)
#define PA7_ALT1                (PA7  | ALT1)
#define PA7_ALT2                (PA7  | ALT2)
#define PA9_ALT1                (PA9  | ALT1)
#define PA10_ALT1               (PA10 | ALT1)
#define PA15_ALT1               (PA15 | ALT1)
#define PB0_ALT1                (PB0  | ALT1)
#define PB1_ALT1                (PB1  | ALT1)
#define PB3_ALT1                (PB3  | ALT1)
#define PB4_ALT1                (PB4  | ALT1)
#define PB5_ALT1                (PB5  | ALT1)
#define PB6_ALT1                (PB6  | ALT1)
#define PB7_ALT1                (PB7  | ALT1)
#define PB8_ALT1                (PB8  | ALT1)
#define PB10_ALT1               (PB10 | ALT1)
#define PB13_ALT1               (PB13 | ALT1)
#define PB14_ALT1               (PB14 | ALT1)
#define PB15_ALT1               (PB15 | ALT1)
#define PC1_ALT1                (PC1  | ALT1)
#define PC10_ALT1               (PC10 | ALT1)
#define PC11_ALT1               (PC11 | ALT1)
#define PH3_ALT1                (PH3  | ALT1)

#define NUM_DIGITAL_PINS        47
#define NUM_ANALOG_INPUTS       6

/*----------------------------------------------------------------------------
 *        Board parts (names follow the schematic)
 *----------------------------------------------------------------------------*/
// LEDs, active high through 1 kOhm
#define LED1_A                  PC10
#define LED1_B                  PC11
#define LED2_A                  PC12
#define LED2_B                  PB4
#ifndef LED_BUILTIN
  #define LED_BUILTIN           LED1_A
#endif

// Buttons, read HIGH when pressed (external 10 kOhm pull-down)
#define BUTTON_USER1            PB5      // SW2
#define BUTTON_USER2            PB2      // SW1
#define BUTTON_PRESSED          HIGH
#ifndef USER_BTN
  #define USER_BTN              BUTTON_USER1
#endif

// Grove I2C power switch (TPS22919), HIGH = on
#define GROVE_I2C_POWER         PA4

// mikroBUS socket (J5, J6)
#define MIKROBUS_AN             PA0
#define MIKROBUS_RST            PC3
#define MIKROBUS_CS             PB0
#define MIKROBUS_PWM            PB10
#define MIKROBUS_INT            PC9

// microSD (K7), SPI mode on SPI1
#define SD_CS                   PC8
#define SD_DETECT               PD2      // LOW = card inserted
#define SD_DETECT_LEVEL         LOW

// Clock output (MCO1 on D9)
#define MCO_PIN                 PA8

/*----------------------------------------------------------------------------
 *        Peripheral defaults
 *----------------------------------------------------------------------------*/
// I2C1: Grove K4, Qwiic K8, mikroBUS, Arduino header
#ifndef PIN_WIRE_SDA
  #define PIN_WIRE_SDA          PB7
#endif
#ifndef PIN_WIRE_SCL
  #define PIN_WIRE_SCL          PB6
#endif

// SPI1: Arduino header, mikroBUS, microSD
#ifndef PIN_SPI_SS
  #define PIN_SPI_SS            PA15
#endif
#ifndef PIN_SPI_MOSI
  #define PIN_SPI_MOSI          PA7
#endif
#ifndef PIN_SPI_MISO
  #define PIN_SPI_MISO          PA6
#endif
#ifndef PIN_SPI_SCK
  #define PIN_SPI_SCK           PA5
#endif

// Timers used by tone() and Servo, so they don't take a PWM pin
#ifndef TIMER_TONE
  #define TIMER_TONE            TIM6
#endif
#ifndef TIMER_SERVO
  #define TIMER_SERVO           TIM7
#endif

// USART1 on D0/D1 (also Grove UART K6 and mikroBUS J6).
// With USB CDC enabled (default), 'Serial' is USB and this port is 'Serial1'.
#ifndef SERIAL_UART_INSTANCE
  #define SERIAL_UART_INSTANCE  1
#endif
#ifndef PIN_SERIAL_RX
  #define PIN_SERIAL_RX         PA10
#endif
#ifndef PIN_SERIAL_TX
  #define PIN_SERIAL_TX         PA9
#endif

// Crystals fitted on the board
#define HSE_VALUE_BOARD         16000000UL
#define LSE_VALUE_BOARD         32768UL

// SDMMC signals not available
#define SDMMC_CDIR_NA

// Extra HAL modules
#if !defined(HAL_DAC_MODULE_DISABLED)
  #define HAL_DAC_MODULE_ENABLED
#endif
#if !defined(HAL_I3C_MODULE_DISABLED)
  #define HAL_I3C_MODULE_ENABLED
#endif
#if !defined(HAL_OSPI_MODULE_DISABLED)
  #define HAL_OSPI_MODULE_ENABLED
#endif
#if !defined(HAL_SD_MODULE_DISABLED)
  #define HAL_SD_MODULE_ENABLED
#endif

// Alternate SYS_WKUP definition
#define PWR_WAKEUP_PIN1_1
#define PWR_WAKEUP_PIN2_1
#define PWR_WAKEUP_PIN3_1
#define PWR_WAKEUP_PIN4_1
#define PWR_WAKEUP_PIN4_2
#define PWR_WAKEUP_PIN5_1
#define PWR_WAKEUP_PIN6_1
#define PWR_WAKEUP_PIN7_1
#define PWR_WAKEUP_PIN8_1

/*----------------------------------------------------------------------------
 *        Arduino objects - C++ only
 *----------------------------------------------------------------------------*/
#ifdef __cplusplus
  #ifndef SERIAL_PORT_MONITOR
    #define SERIAL_PORT_MONITOR   Serial
  #endif
  #ifndef SERIAL_PORT_HARDWARE
    #define SERIAL_PORT_HARDWARE  Serial1
  #endif
#endif

#ifdef __cplusplus
extern "C" {
#endif
/* Reboot into the STM32 ROM USB-DFU bootloader (used by the 1200-baud upload touch). */
void u385_enter_bootloader(void);
#ifdef __cplusplus
}
#endif
